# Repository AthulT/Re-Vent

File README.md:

# Re-Vent
The official Repository for Re-Vent: A Low Cost Portable Ventilator for Emergencies
This project is done by Athul T, Devika Shaj, Gaadha P Nath, and Shyama H of College of Engineering Trivandrum.
The project is guided by Dr. Sajith Vijayaraghavan, Asst Professor, College of Engineering Trivandrum, and Mr. Rahul CS Nair, Engineer, Rajiv Gandhi Centre for Biotechnology.
Those who wish to use, and modify the code and files are free to do so, strictly following the terms and conditions of the GNU General Public License version 3.0(GPL-3.0 License), giving due credit. For further details, refer the LICENSE file.

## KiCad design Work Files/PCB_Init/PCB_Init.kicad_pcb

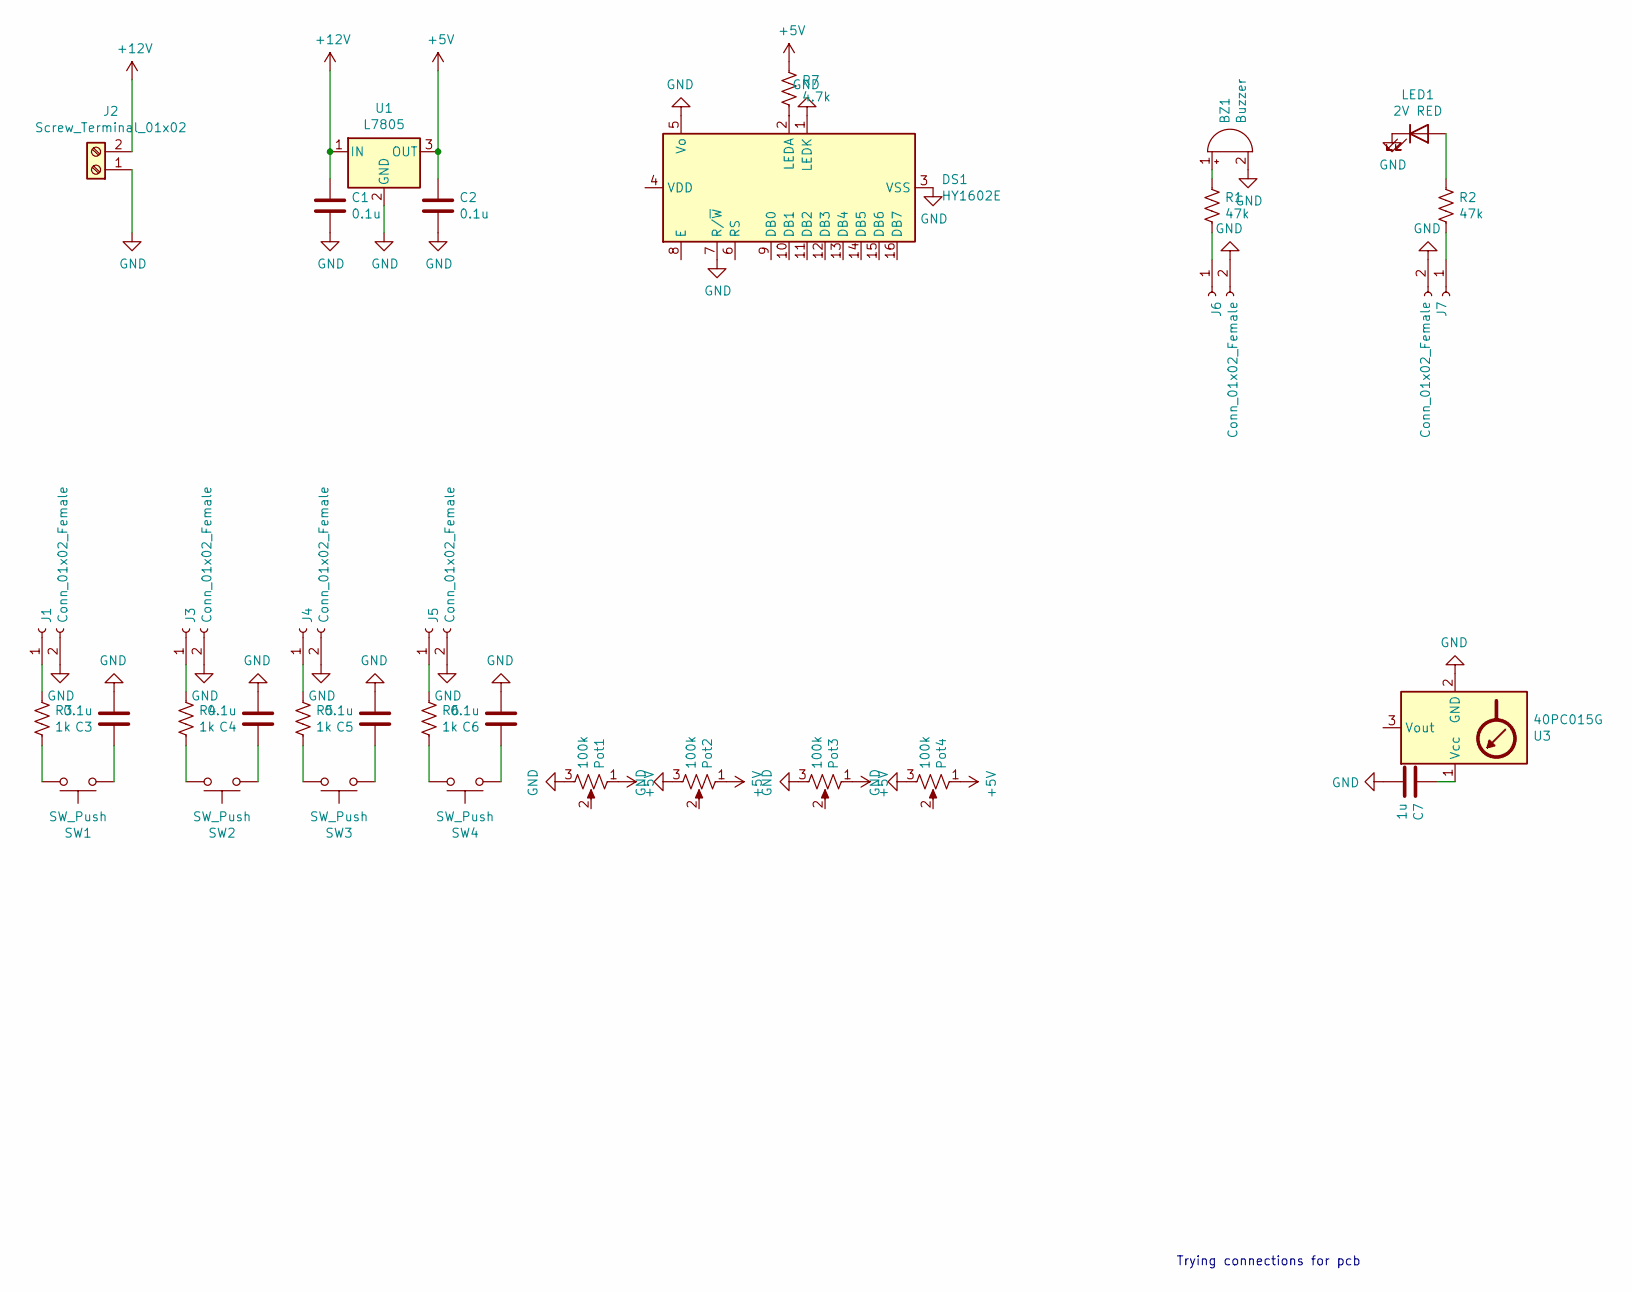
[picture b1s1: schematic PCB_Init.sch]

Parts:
BZ1: Buzzer; Buzzer_12x9.5RM7.6
C1, C2, C3, C4, C5, C6: 0.1u; CP_Radial_D8.0mm_P5.00mm
C7: 1u; CP_Radial_D8.0mm_P5.00mm
DS1: HY1602E
J1, J3, J4, J5, J6, J7: Conn_01x02_Female; PinHeader_1x02_P2.54mm_Vertical
J2: Screw_Terminal_01x02; TerminalBlock_Altech_AK300-2_P5.00mm
LED1: 2V RED; LED_D3.0mm
Pot1, Pot2, Pot3, Pot4: 100k; Potentiometer_Bourns_3296W_Vertical
R1, R2: 47k; R_Axial_DIN0207_L6.3mm_D2.5mm_P10.16mm_Horizontal
R3, R4, R5, R6: 1k; R_Axial_DIN0207_L6.3mm_D2.5mm_P10.16mm_Horizontal
R7: 4.7k; R_Axial_DIN0207_L6.3mm_D2.5mm_P10.16mm_Horizontal
SW1, SW2, SW3, SW4: SW_Push; SW_CW_GPTS203211B
U1: L7805; TO-3P-3_Vertical
U3: 40PC015G; Honeywell_40PCxxxG1A

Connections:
+5V: C2.1, Pot1.1, Pot2.1, Pot3.1, Pot4.1, R7.1, U1.3 (OUT)
+12V: C1.1, J2.2, U1.1 (IN)
GND: BZ1.2 (+), C1.2, C2.2, C3.2, C4.2, C5.2, C6.2, C7.2, DS1.1 (LEDK), DS1.3 (VSS), DS1.5 (Vo), DS1.7 (R/~W), J1.2, J2.1, J3.2, J4.2, J5.2, J6.2, J7.2, LED1.1 (K), Pot1.3, Pot2.3, Pot3.3, Pot4.3, U1.2 (GND), U3.2 (GND)
unnamed: BZ1.1 (-), R1.1
unnamed: C3.1, SW1.1
unnamed: C4.1, SW2.1
unnamed: C5.1, SW3.1
unnamed: C6.1, SW4.1
unnamed: C7.1, U3.1 (Vcc)
unnamed: DS1.2 (LEDA), R7.2
unnamed: J1.1, R3.1
unnamed: J3.1, R4.1
unnamed: J4.1, R5.1
unnamed: J5.1, R6.1
unnamed: J6.1, R1.2
unnamed: J7.1, R2.2
unnamed: LED1.2 (A), R2.1
unnamed: R3.2, SW1.2
unnamed: R4.2, SW2.2
unnamed: R5.2, SW3.2
unnamed: R6.2, SW4.2

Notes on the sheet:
Trying connections for pcb

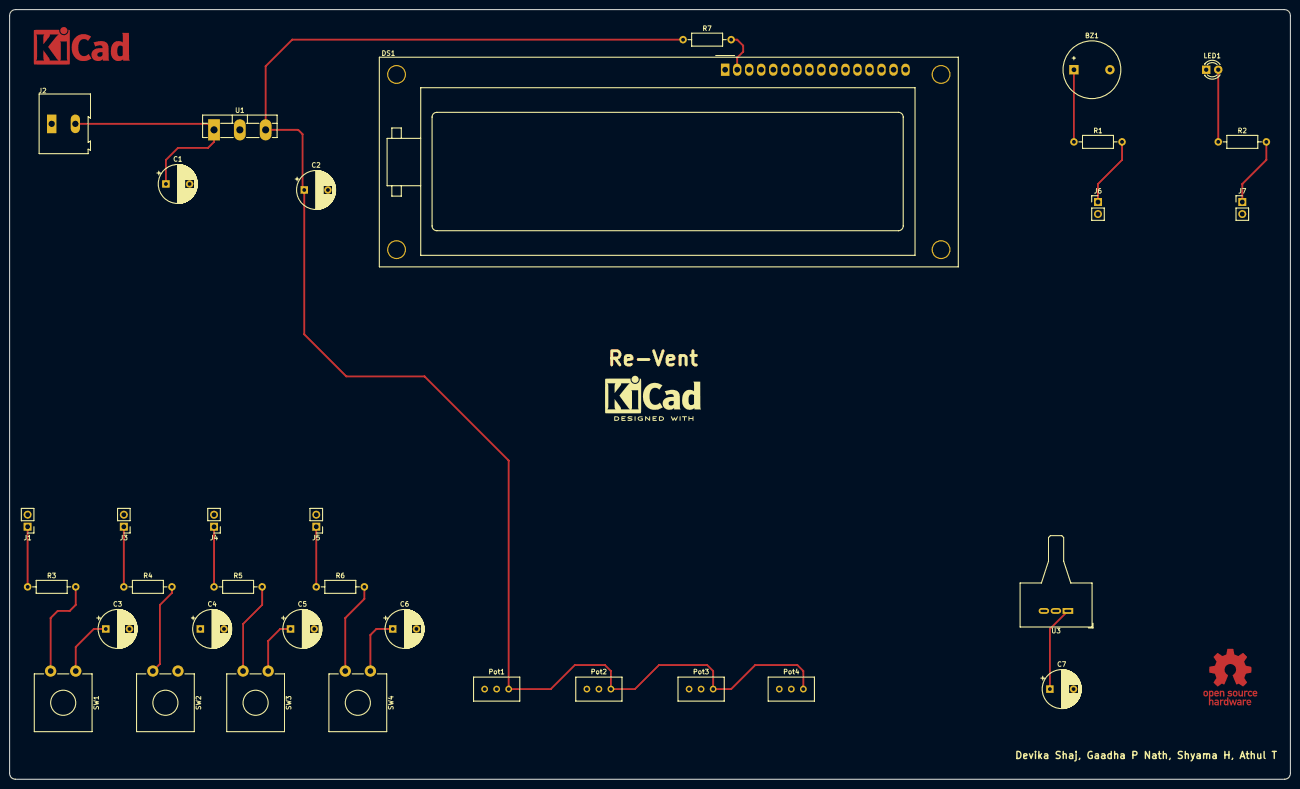
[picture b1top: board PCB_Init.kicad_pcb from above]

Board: 2 copper layers, 270.5 x 162.6 mm, 34 parts (0 on the bottom side), 21 nets.

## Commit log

2021-03-14 First commit from local repo
2021-03-14 second commit from local repo
2021-03-16 third commit
2021-03-18 KiCad libraries: Arduino Mega, MIT Ventilator files
2021-03-18 KiCad libraries: Arduino Mega, MIT Ventilator files, organized
2021-03-25 add oxymeter refernce file
2021-03-25 add MIT E-Vent arduino files
2021-04-01 First base design for pcb, have to work on it
2021-04-06 Wired connections in Eeschema, would be changed in later development
2021-04-06 Wired connections in Eeschema, would be changed in later development 2
2021-04-10 Added KiCAD file with AtMega2560 details and pulse oxi
2021-04-11 Added KiCAD file with AtMega2560 details and pulse oxi 2
2021-04-12 Started designing PCB
2021-04-12 Started designing PCB2
2021-04-12 Started designing PCB3
2021-04-12 Started designing ing PCB 4
2021-04-12 Started designing ing PCB 6
2021-04-21 Plotted gerber files for initial idea
2021-04-21 Plotted gerber files for initial idea1
2021-04-21 Plotted gerber files for initial idea2
2021-04-21 Plotted gerber files for initial idea3
2021-04-22 PCB update with LCD 16x2
2021-04-24 Added temporary design for HX710B module
2021-04-24 Added temporary design for HX710B module2
2021-04-24 Added temporary design for HX710B module3
